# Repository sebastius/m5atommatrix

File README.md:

# m5atommatrix
4x4 M5 atoms, connected and powered through usb-c

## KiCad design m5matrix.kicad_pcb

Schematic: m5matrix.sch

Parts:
H1, H2, H3, H4: MountingHole; MountingHole_3.2mm_M3
J1: USB_C_Receptacle_USB2.0; USB_C_Receptacle_HRO_TYPE-C-31-M-12
J2: Conn_01x04_Male; JST_PH_S4B-PH-K_1x04_P2.00mm_Horizontal
R1, R2: 5.1k; R_0805_2012Metric_Pad1.15x1.40mm_HandSolder
R3, R4: R; R_0805_2012Metric_Pad1.15x1.40mm_HandSolder
U1, U2, U3, U4, U5, U6, U7, U8, U9, U10, U11, U12, U13, U14, U15, U16: atommatrix; M5atom matrix

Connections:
+3V3: R3.1, R4.1, U12.1
+5V: J1.A4 (VBUS), J1.A9 (VBUS), J1.B4 (VBUS), J1.B9 (VBUS), J2.2, U1.8, U2.8, U3.8, U4.8, U5.8, U6.8, U7.8, U8.8, U9.8, U10.8, U11.8, U12.8, U13.8, U14.8, U15.8, U16.8
/I2C_SCL: J2.4, R4.2, U1.7, U2.7, U3.7, U4.7, U5.7, U6.7, U7.7, U8.7, U9.7, U10.7, U11.7, U12.7, U13.7, U14.7, U15.7, U16.7
/I2C_SDA: J2.3, R3.2, U1.6, U2.6, U3.6, U4.6, U5.6, U6.6, U7.6, U8.6, U9.6, U10.6, U11.6, U12.6, U13.6, U14.6, U15.6, U16.6
GND: J1.A1 (GND), J1.A12 (GND), J1.B1 (GND), J1.B12 (GND), J1.S1 (SHIELD), J2.1, R1.1, R2.1, U1.9, U2.9, U3.9, U4.9, U5.9, U6.9, U7.9, U8.9, U9.9, U10.9, U11.9, U12.9, U13.9, U14.9, U15.9, U16.9
unnamed: J1.A5 (CC1), R1.2
unnamed: J1.B5 (CC2), R2.2

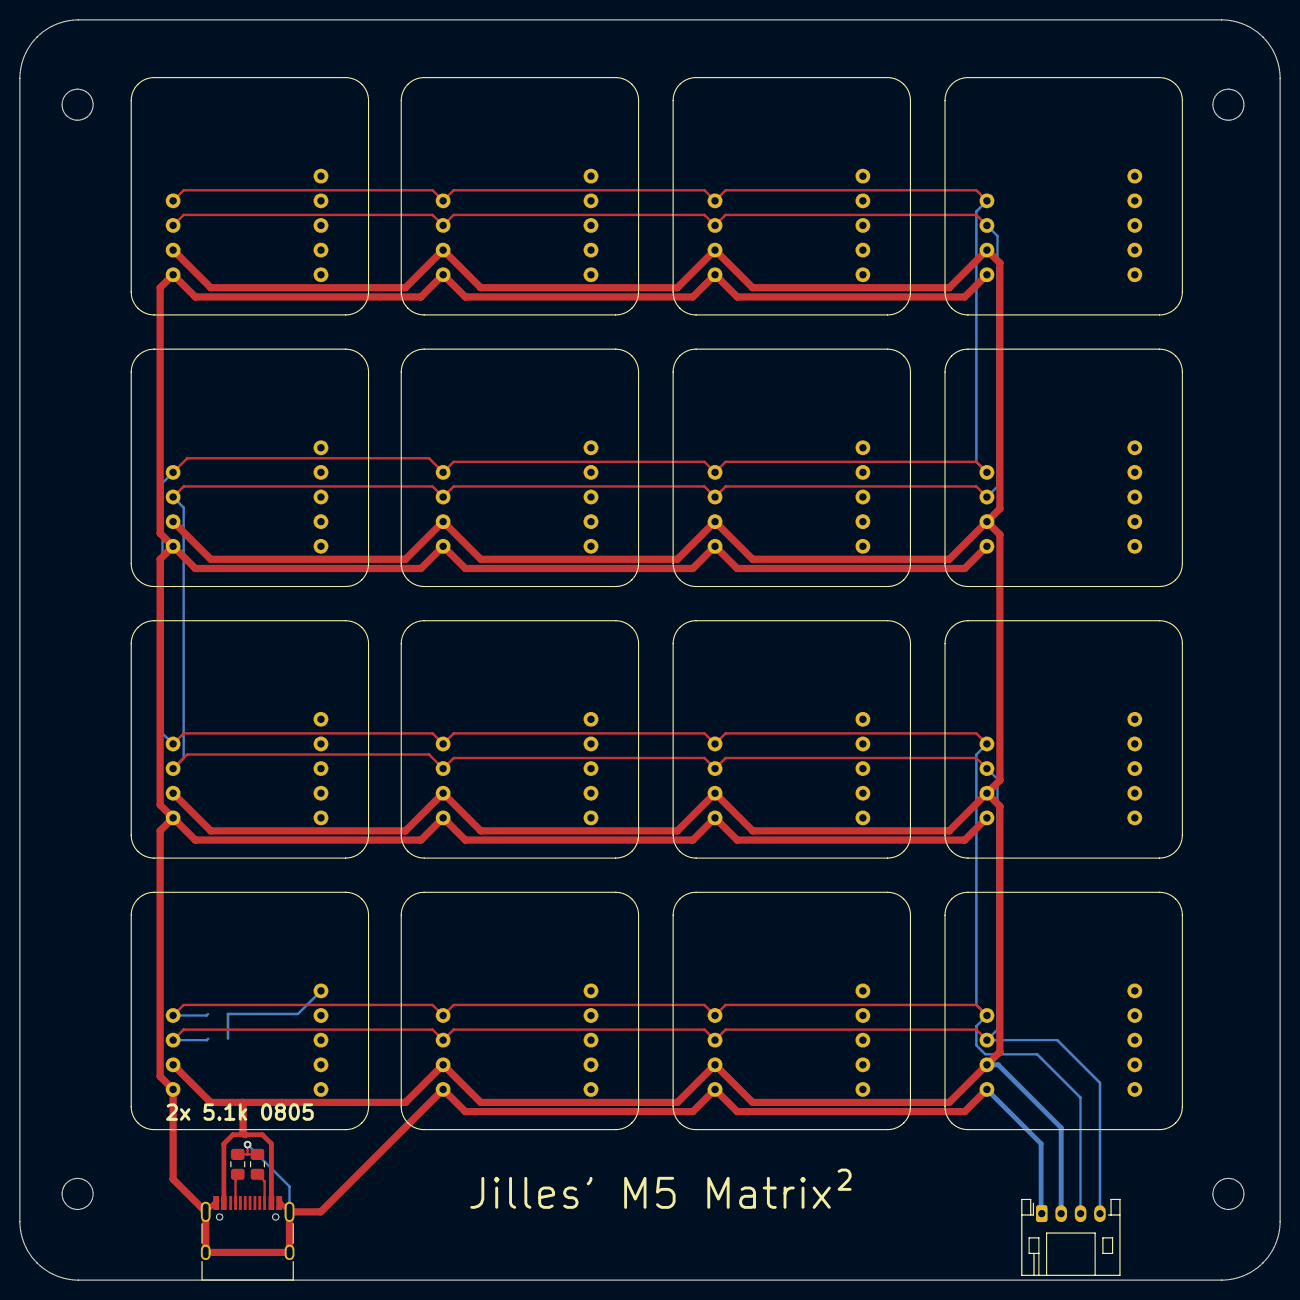
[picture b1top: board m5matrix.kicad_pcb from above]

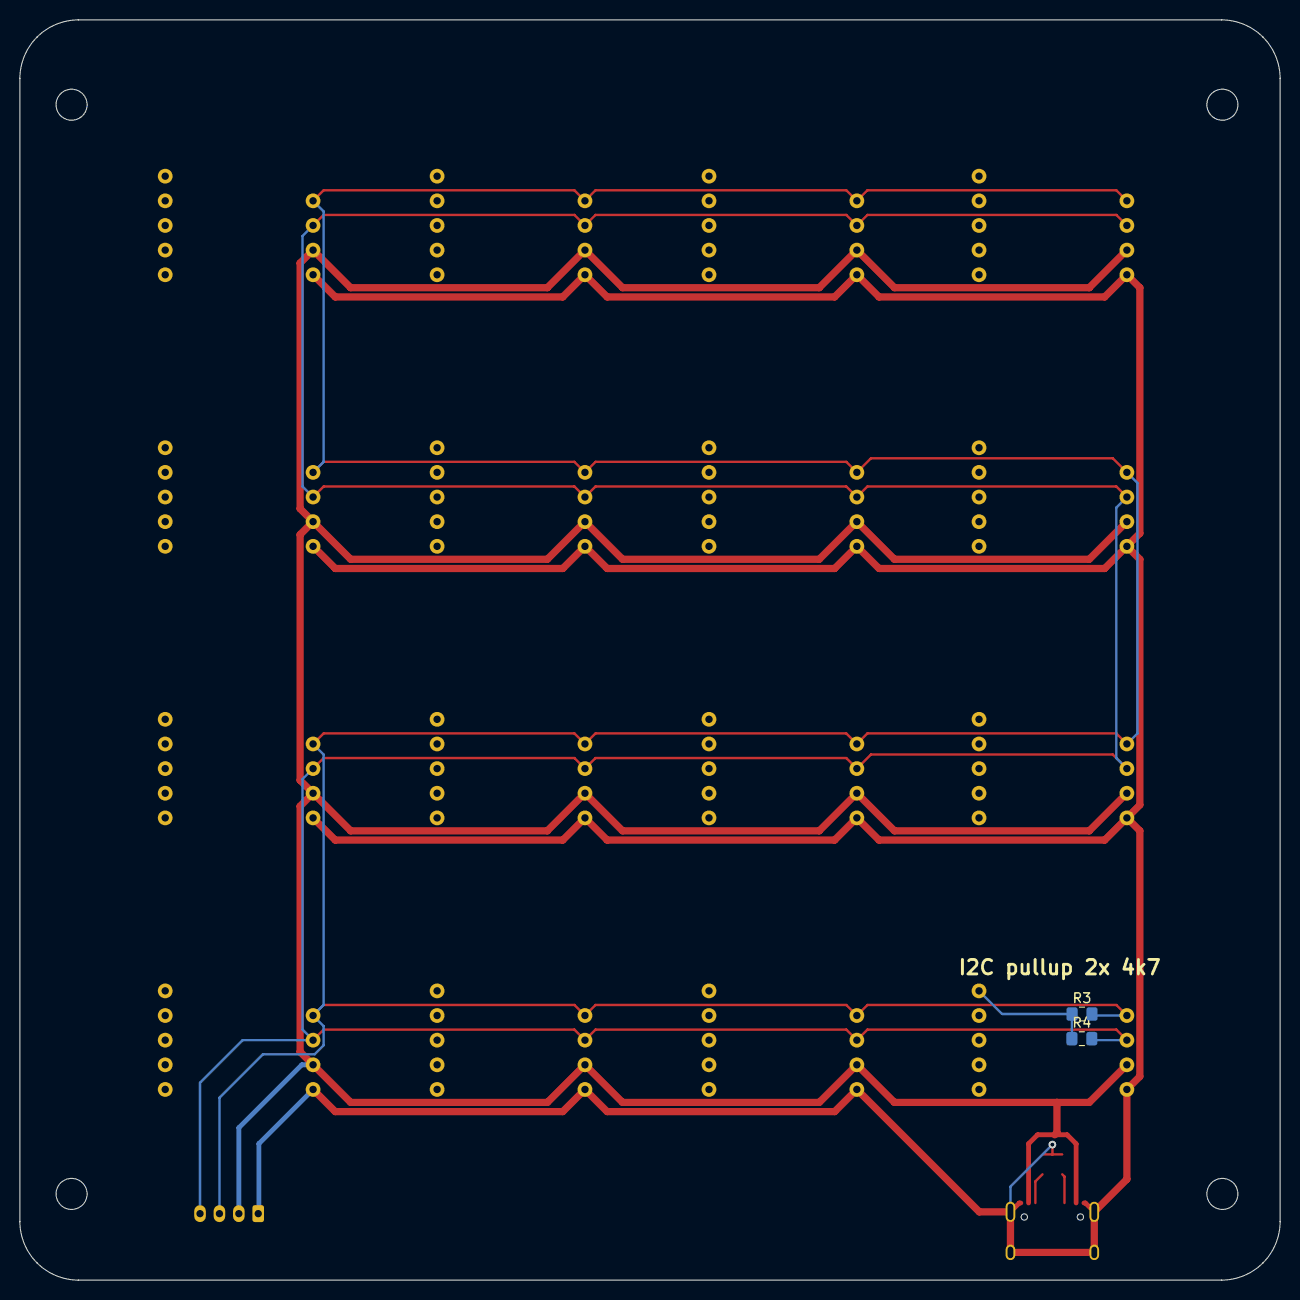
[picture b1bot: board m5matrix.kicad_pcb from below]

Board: 2 copper layers, 129.9 x 129.9 mm, 26 parts (2 on the bottom side), 7 nets.

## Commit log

2021-08-24 Initial commit
    and probably the last.
2021-08-24 Picture
